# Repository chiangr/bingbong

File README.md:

# bingbong

The current interactive product site, engineering references, and hardware working files in one checkout. Start with [SESSION_HANDOFF.md](SESSION_HANDOFF.md) for the accepted design direction, source authority, verification results, and remaining work.

This handoff branch is `codex/assembly-handoff-2026-09-22` in [chiangr/bingbong](https://github.com/chiangr/bingbong). It preserves the earlier `master` history and mirrors the local project layout: the former repository-root firmware now lives under `firmware/`.

## Run the site

Install Node.js 24 LTS (or 22.12+) and run:

```sh
git clone --single-branch --branch codex/assembly-handoff-2026-09-22 https://github.com/chiangr/bingbong.git
cd bingbong/site
npm ci
npm run dev
```

Open http://localhost:5173/#inside for the exploded assembly study, or http://localhost:5173/ for the full fifteen-chapter experience. [The standalone HTML](site/artifact/bingbong.html) also opens directly in a browser without installing dependencies.

For a production preview:

```sh
npm run build
npm run preview
```

Open http://localhost:4173/#inside. Servers must be started on each laptop; no remote service is required.

## Project map

| Path | Contents |
| --- | --- |
| [site/](site/) | Current Three.js/Vite experience, all assets, source, scripts and documentation |
| [site/qa/](site/qa/) | Saved tests, 240 layout captures, independent reviews, Lighthouse report and videos |
| [DESIGN_MANUFACTURING_REPORT_2026-09-19.md](DESIGN_MANUFACTURING_REPORT_2026-09-19.md) | Latest engineering authority, including conflicts and open decisions |
| [REDESIGN_DECISION_2026-09-12.md](REDESIGN_DECISION_2026-09-12.md) | Earlier engineering decisions; superseded where the September 19 report conflicts |
| [firmware/](firmware/) | Existing ESP32-S2/BG95 bring-up code and current KiCad working files in `bingbong_pcb/` |
| [cad/](cad/), [cad-v2/](cad-v2/) | Existing mechanical and PCB design exports; these are not final production CAD for the illustrated reference build |
| [pcbway-fab/](pcbway-fab/), [datasheets/](datasheets/), [bom-scratch/](bom-scratch/) | Fabrication exports, component references and supporting analysis |

See [site/README.md](site/README.md) for interactions and verification commands. The website uses the engineering report's reference geometry; existing hardware files and firmware do not constitute a completed implementation of that design.

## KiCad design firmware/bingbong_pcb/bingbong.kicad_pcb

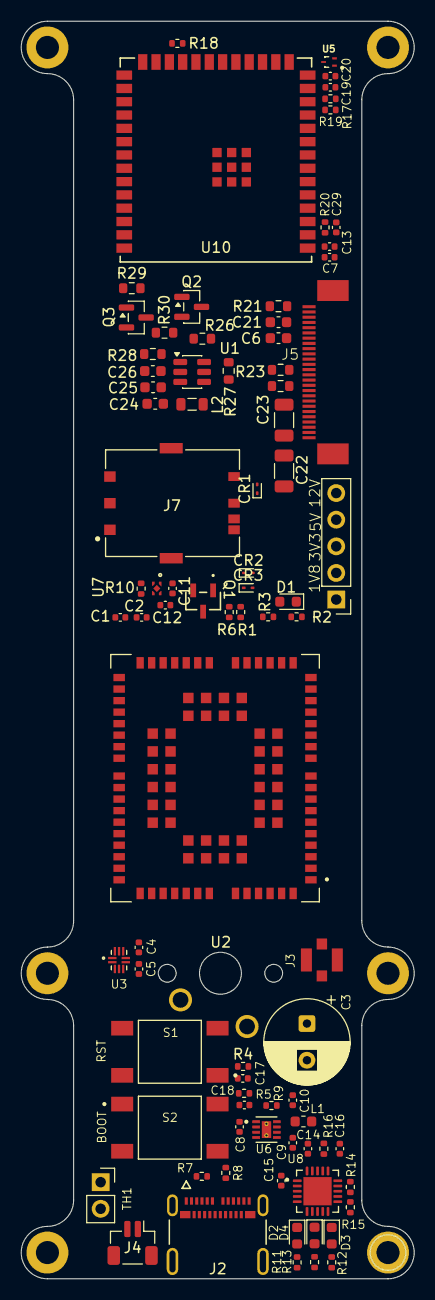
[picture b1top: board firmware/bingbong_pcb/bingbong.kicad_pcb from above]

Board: 2 copper layers, 37.5 x 120.0 mm, 85 parts (1 on the bottom side), 60 nets, no tracks yet.

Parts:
C1, C4, C5, C7, C17, C18, C19: 0.1uF; C_0402_1005Metric
C2, C11, C12, C29: 1uF; C_0402_1005Metric
C3: 470 uF; CP_Radial_D8.0mm_P3.50mm
C6, C21: 0.1uF; C_0603_1608Metric
C8, C9, C15: 10uF; C_0402_1005Metric
C10, C13, C20: 22uF; C_0402_1005Metric
C14, C16: 4.7uF; C_0402_1005Metric
C22, C23: 4.7uF; C_1206_3216Metric
C24, C25: 1uF; C_0603_1608Metric
C26: 220pF; C_0603_1608Metric
CR1, CR2, CR3: PESD5V0F1BLD_315; D_SOD-923
D1: RED LED; LED_0603_1608Metric
D2, D3, D4: LED; LED_0603_1608Metric
J2: 1054500101; MOLEX_1054500101
J3: CONMHF1-SMD-T; TE_CONMHF1-SMD-T
J4: Conn_01x02_Pin; JST_SH_BM02B-SRSS-TB_1x02-1MP_P1.00mm_Vertical
J5: Conn_01x28_Socket; Conn_Zif_26Pin
J6: Conn_01x05_Pin; PinHeader_1x05_P2.54mm_Vertical
J7: 2452808-1; TE_2452808-1
L1: 2.2uH; L_0603_1608Metric
L2: 22uH; L_0805_2012Metric
Q1: SOT-23; SOT-23-3_1P4X3P040_ONS
Q2: FDN340P; SOT-23
Q3: SS8050; SOT-23
R1, R14, R15, R18, R20: 10k; R_0402_1005Metric
R2, R6, R9, R10, R16: 100k; R_0402_1005Metric
R3, R11, R12, R13: 1k; R_0402_1005Metric
R4, R5, R17, R19: 0; R_0402_1005Metric
R7, R8: 5.1k; R_0402_1005Metric
R21: 680k; R_0603_1608Metric
R22, R23, R26, R30: 10k; R_0603_1608Metric
R27: 110k; R_0603_1608Metric
R28: 2k; R_0603_1608Metric
R29: 1k; R_0603_1608Metric
S1, S2: TS04-66-70-BK-100-SMT; SW_TS04-66-70-BK-100-SMT
SW1: SW_Push; SW_Cherry_MX_1.00u_PCB
TH1: 10k; PinSocket_1x02_P2.54mm_Vertical
U1: SOT-23-6
U2: BG95M3LA-64-SGNS; XCVR_BG95M3LA-64-SGNS
U3: SN74AVC2T245RSWR; QFN40P180X140X55-10N
U5: TPD2EUSB30ADRTR; SOTFL35P100X50-3N
U6: TPS62172DSGR; SON50P200X200X80-9N
U7: MIC5504-1.8YMT-TR; TDFN1010-4LD-PL-2_MCH
U8: MCP73871-2CCI_ML; QFN50P400X400X100-21N
U10: ESP32-S2-SOLO-2U-N4; ESP32-S2-SOLO-2U_EXP

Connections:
+1.8V: C4.1, C11.1, J6.2, R2.1, U3.7 (VCCA), U7.1 (VOUT)
+3.3V: C5.1, C6.1, C7.1, C9.1, C10.1, C12.1, C13.1, C21.1, J5.19, J5.21, J5.22, J6.3, L1.1, Q2.2 (S), R3.2, R9.1, R11.1, R12.1, R13.1, R20.2, R22.2, R23.2, R30.1, SW1.1, U3.6 (VCCB), U3.10 (DIR1), U6.6 (VOS), U7.4 (VIN), U8.9 (~TE), U10.2 (3V3)
+5V: C15.1, J2.A4 (VBUS_A4), J2.A9 (VBUS_A9), J2.B4 (VBUS_B4), J2.B9 (VBUS_B9), J6.4, U8.2 (VPCC), U8.18 (IN), U8.19 (IN__1)
+12V: C22.1, C25.1, C26.1, J5.2, J5.25, J6.5, R27.2, U1.2 (VOUT)
/ANT_MAIN: J3.1, U2.60 (ANT_MAIN)
/BG95 RX: U2.34 (MAIN_RXD), U3.9 (A2)
/BG95 TOGGLE POWER: R1.1, R6.1, U10.20 (IO12)
/BG95 TX: U2.35 (MAIN_TXD), U3.8 (A1)
/BG95_CLK: CR2.1, J7.C3 (CLK), U2.46 (USIM_CLK)
/BG95_IO: CR1.1, J7.C7 (I/O), U2.45 (USIM_DATA)
/BG95_RST: CR3.1, J7.C2 (RST), U2.44 (USIM_RST)
/BG95_VCC: J7.C1 (VCC), U2.43 (USIM_VDD)
/BOOT: R5.2, U10.27 (IO0)
/BTN: R18.2, SW1.2, U10.23 (IO21)
/CHARGE EN: R16.2, U8.17 (CE), U10.22 (IO14)
/EN: C29.2, R4.2, R20.1, U10.3 (EN)
/ESP32 RX: U3.5 (B1), U10.38 (IO2)
/ESP32 TX: U3.4 (B2), U10.39 (IO1)
/IO19: R19.2, U10.13 (IO19)
/IO20: R17.2, U10.14 (IO20)
/MIC EN: R10.2, U7.3 (EN), U10.21 (IO13)
/OLED RST: J5.16, U10.17 (IO9)
/OLED SCL: J5.12, R23.1, U10.18 (IO10)
/OLED SDA: J5.10, J5.11, R22.1, U10.19 (IO11)
/R1200 CE: U1.1 (CE), U10.12 (IO8)
/R1200 PWR EN: R29.2, U10.11 (IO18)
/SIM SW: J7.SW, U10.24 (IO33)
/SYS LOAD: C8.1, C14.1, U6.2 (VLN), U6.3 (EN), U8.1 (OUT), U8.20 (OUT__1)
/USB D+: C19.1, C20.1, J2.A6 (D1+), J2.B6 (D2+), R17.1, U5.1 (D+)
/USB D-: J2.A7 (D1-), J2.B7 (D2-), R19.1, U5.2 (D-)
/VBAT: C1.1, C2.1, C3.1, J4.2, TH1.2, U2.32 (VBAT_BB), U2.33 (VBAT_BB__1), U2.52 (VBAT_RF), U2.53 (VBAT_RF__1), U8.5 (THERM)
GND: C1.2, C2.2, C3.2, C4.2, C5.2, C6.2, C7.2, C8.2, C9.2, C10.2, C11.2, C12.2, C13.2, C14.2, C15.2, C16.2, C17.2, C18.2, C19.2, C20.2, C21.2, C22.2, C23.2, C24.2, C25.2, C29.1, CR1.2, CR2.2, CR3.2, J2.A1 (GND_A1), J2.A12 (GND_A12), J2.B1 (GND_B1), J2.B12 (GND_B12), J2.SH1 (SHIELD3), J2.SH2 (SHIELD4), J2.SH3 (SHIELD1), J2.SH4 (SHIELD2), J3.2, J3.3, J3.4, J4.1, J5.4, J5.5, J5.6, J5.7, J5.8, J5.9, J5.13, J5.14, J5.15, J5.17, J5.18, J5.20, J5.23, J5.27, J5.28, J6.1, J7.C5 (GND), J7.GND8 (SH), J7.GND9 (SH__1), Q1.1 (E), Q3.2 (E), R6.2, R7.2, R8.1, R10.1, R14.1, R15.1, R16.1, R18.1, R21.2, R26.1, S1.2, S1.4, S2.2, S2.4, TH1.1, U1.5 (GND), U2.3 (GND), U2.31 (GND__1), U2.47 (USIM_GND), U2.48 (GND__2), U2.50 (GND__3), U2.54 (GND__4), U2.55 (GND__5), U2.58 (GND__6), U2.59 (GND__7), U2.61 (GND__8), U2.62 (GND__9), U2.67 (GND__10), U2.68 (GND__11), U2.69 (GND__12), U2.70 (GND__13), U2.71 (GND__14), U2.72 (GND__15), U2.73 (GND__16), U2.74 (GND__17), U2.79 (GND__18), U2.80 (GND__19), U2.81 (GND__20), U2.82 (GND__21), U2.89 (GND__22), U2.90 (GND__23), U2.91 (GND__24), U2.100 (GND__25), U2.101 (GND__26), U2.102 (GND__27), U3.1 (DIR2), U3.2 (~OE), U3.3 (GND), U5.3 (GND), U6.1 (PGND), U6.4 (AGND), U6.5 (FB), U6.9 (EPAD), U7.2 (GND), U7.5 (GND), U8.3 (SEL), U8.4 (PROG2), U8.10 (VSS__1), U8.11 (VSS), U8.21 (EP), U10.1 (GND), U10.40 (GND), U10.41 (GND), U10.42 (GND), U10.43 (GND), U10.44 (GND), U10.45 (GND), U10.46 (GND), U10.47 (GND), U10.48 (GND), U10.49 (GND)
unnamed: C17.1, R4.1, S1.1, S1.3
unnamed: C18.1, R5.1, S2.1, S2.3
unnamed: C26.2, R28.2
unnamed: D1.2 (A), R3.1
unnamed: D1.1 (K), U2.21 (NET_STATUS)
unnamed: D2.2 (A), R11.2
unnamed: D2.1 (K), U8.6 (~PG)
unnamed: D3.2 (A), R12.2
unnamed: D3.1 (K), U8.8 (STAT1/*LBO)
unnamed: D4.2 (A), R13.2
unnamed: D4.1 (K), U8.7 (STAT2)
unnamed: J2.A5 (CC1), R7.1
unnamed: J2.B5 (CC2), R8.2
unnamed: C23.1, J5.3
unnamed: J5.24, R21.1
unnamed: Q1.2 (B), R1.2
unnamed: Q1.3 (C), U2.15 (PWRKEY)
unnamed: C24.1, L2.1, Q2.3 (D), U1.3 (VDD)
unnamed: Q2.1 (G), Q3.3 (C), R30.2
unnamed: Q3.1 (B), R29.1
unnamed: L2.2, U1.4 (Lx)
unnamed: R26.2, R27.1, R28.1, U1.6 (VFB)
unnamed: R2.2, U2.17 (~RESET)
unnamed: R9.2, U6.8 (PG)
unnamed: L1.2, U6.7 (SW)
unnamed: R14.2, U8.13 (PROG1)
unnamed: R15.2, U8.12 (PROG3)
unnamed: C16.1, U8.14 (VBAT__1), U8.15 (VBAT), U8.16 (VBAT_SENSE)

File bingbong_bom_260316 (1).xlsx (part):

Ryan Chiang |  | rychi@berkeley.edu |  |  |  |  |  |  |  |  |  |  |  |  |  | Total Price for Project
 |  |  |  |  |  |  |  |  |  |  |  |  |  |  |  | 68.7
Quantity | Purchase Status | Description (include component value if applicable) | Purchase URL | Reference Designator | Package/Case | Type | Assembly (YES/NO) | Side | Manufacturer Part # | Digi-key Part#/SKU | Price/unit ($) | Datasheet Link |  | Multiple | Total Qty | Total Price/part ($)
1.0 | Ordered | 470 µF 16 V Aluminum Electrolytic Capacitors Radial, Can 8000 Hrs @ 105°C | https://www.digikey.com/en/products/detail/rubycon/16ZLH470M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 | C3 | Radial, Can | Through Hole | YES | TOP | 16ZLH470MEFCT78X11.5 | 1189-3712-1-ND | 0.42 | https://www.rubycon.co.jp/wp-content/uploads/catalog-aluminu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 |  | 1.0 | 1 | 0.42
4.0 | Ordered | 1 µF ±10% 6.3V Ceramic Capacitor X5R 0402 (1005 Metric) | https://www.digikey.com/en/products/detail/taiyo-yuden/JMK10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 | C2, C11, C12, C29 | 402.0 | SMD | YES | TOP | JMK105BJ105KV-F | 587-1231-2-ND | 0.08 | https://ds.yuden.co.jp/TYCOMPAS/ut/detail?pn=JMK105BJ105KV-F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 |  | 1.0 | 4 | 0.32
7.0 | Ordered | 0.1 µF ±10% 25V Ceramic Capacitor X5R 0402 (1005 Metric) | https://www.digikey.com/en/products/detail/samsung-electro-m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 | C1, C4, C5, C7, C17, C18, C19 | 402.0 | SMD | YES | TOP | CL05A104KA5NNNC | 1276-1043-2-ND | 0.08 | https://mm.digikey.com/Volume0/opasdata/d220001/medias/docus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 |  | 1.0 | 7 | 0.56
2.0 | Ordered | 100 pF ±10% 50V Ceramic Capacitor X7R 0603 (1608 Metric) | https://www.digikey.com/en/products/detail/kemet/C0603C101K5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 | C6, C21 | 603.0 | SMD | YES | TOP | C0603C101K5RACAUTO7411 | 399-C0603C101K5RACAUTO7411CT-ND | 0.12 | https://yageogroup.com/content/datasheet/asset/file/KEM_C102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 |  | 1.0 | 2 | 0.24
2.0 | Ordered | 4.7 µF Molded Tantalum Capacitors 25 V 1206 (3216 Metric) 6Ohm | https://www.digikey.com/en/products/detail/kemet/T491A475K02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 | C22, C23 | 1206.0 | SMD | YES | TOP | T491A475K025AT | 399-10128-1-ND | 0.44 | https://yageogroup.com/content/datasheet/asset/file/KEM_T2005_T491 |  | 1.0 | 2 | 0.88
1.0 | Ordered | 220 pF ±10% 25V Ceramic Capacitor X7R 0603 (1608 Metric) | https://www.digikey.com/en/products/detail/w%C3%BCrth-elektr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 | C26 | 603.0 | SMD | YES | TOP | 8.85012206055E11 | 732-7974-1-ND | 0.1 | https://www.we-online.com/components/products/datasheet/8850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 |  | 1.0 | 1 | 0.1
3.0 | Ordered | 22 µF ±20% 6.3V Ceramic Capacitor X5R 0402 (1005 Metric) | https://www.digikey.com/en/products/detail/murata-electronic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 | C10, C13, C20 | 402.0 | SMD | YES | TOP | GRM158R60J226ME01D | 490-GRM158R60J226ME01DCT-ND | 0.37 | https://search.murata.co.jp/Ceramy/image/img/A01X/G101/ENG/G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 |  | 1.0 | 3 | 1.11
3.0 | Ordered | 10 µF ±20% 10V Ceramic Capacitor X5R 0402 (1005 Metric) | https://www.digikey.com/en/products/detail/murata-electronic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 | C8, C9, C15 | 402.0 | SMD | YES | TOP | GRM155R61A106ME11D | 490-GRM155R61A106ME11DCT-ND | 0.08 | https://search.murata.co.jp/Ceramy/image/img/A01X/G101/ENG/G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 |  | 1.0 | 3 | 0.24
2.0 | Ordered | 4.7 µF ±20% 10V Ceramic Capacitor X5R 0402 (1005 Metric) | https://www.digikey.com/en/products/detail/samsung-electro-m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 | C14, C16 | 402.0 | SMD | YES | TOP | CL05A475MP5NRNC | 1276-1482-1-ND | 0.1 | https://mm.digikey.com/Volume0/opasdata/d220001/medias/docus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 |  | 1.0 | 2 | 0.2
2.0 | Ordered | 1 µF ±10% 16V Ceramic Capacitor X7R 0603 (1608 Metric) | https://www.digikey.com/en/products/detail/kemet/C0603C105K4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 | C24, C25 | 603.0 | SMD | YES | TOP | C0603C105K4RACTU | 399-C0603C105K4RACTUCT-ND | 0.08 | https://yageogroup.com/content/datasheet/asset/file/KEM_C100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 |  | 1.0 | 2 | 0.16
3.0 | Ordered | Clamp Ipp Tvs Diode Surface Mount SOD-923 | https://www.digikey.com/en/products/detail/onsemi/ESD9B5.0ST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 | CR1, CR2, CR3 | SOD-923 | SMD | YES | TOP | ESD9B5.0ST5G | ESD9B5.0ST5GOSCT-ND | 0.1 | https://www.digikey.com/en/products/detail/onsemi/ESD9B5.0ST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 |  | 1.0 | 3 | 0.3
2.0 | Ordered | Red 630nm LED Indication - Discrete 1.9V 0603 (1608 Metric) | https://www.digikey.com/en/products/detail/w-rth-elektronik/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 | D1, D3 | 603.0 | SMD | YES | TOP | 150060SS75000 | 732-4979-1-ND | 0.15 | https://www.digikey.com/en/products/detail/w-rth-elektronik/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 |  | 1.0 | 2 | 0.3
2.0 | Ordered | Green 573nm LED Indication - Discrete 2V 0603 (1608 Metric) | https://www.digikey.com/en/products/detail/w%C3%BCrth-elektr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 | D2, D4 | 603.0 | SMD | YES | TOP | 150060VS55040 | 732-12017-1-ND | 0.19 | https://www.we-online.com/components/products/datasheet/1500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 |  | 1.0 | 2 | 0.38
1.0 | Ordered | USB-C (USB TYPE-C) USB 3.2 Gen 2 (USB 3.1 Gen 2, Superspeed + (USB 3.1)) Recept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 | https://www.digikey.com/en/products/detail/molex/1054500101/5843891 | J2 | -- | SMD, Through Hole | YES | TOP | 1.054500101E9 | WM12856CT-ND | 2.4 | https://www.molex.com/pdm_docs/ps/PS-105448-001.pdf |  | 1.0 | 1 | 2.4
1.0 | Ordered | U.FL (UMCC) Connector Jack, Male Pin 50 Ohms Surface Mount Solder | https://www.digikey.com/en/products/detail/te-connectivity-l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 | J3 | -- | SMD | YES | TOP | CONMHF1-SMD-T | 343-CONMHF1-SMD-TCT-ND | 0.21 | https://www.te.com/commerce/DocumentDelivery/DDEController?A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 |  | 1.0 | 1.0 | 0.21
1.0 | Ordered | Connector Header Surface Mount 2 position 0.039" (1.00mm) | https://www.digikey.com/en/products/detail/jst-sales-america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 | J4 | -- | SMD | YES | TOP | BM02B-SRSS-TBT | 455-BM02B-SRSS-TBTCT-ND | 0.56 | https://www.jst-connector.com/datasheet/jst-connector/BM02B-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 |  | 1.0 | 1.0 | 0.56
1.0 | Ordered | 26 Pins 0.5mm Pitch ZIF Connector (FPC Connector) | https://www.buydisplay.com/white-1-8-inch-256x32-oled-displa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 | J5 | -- | SMD | YES | TOP | -- | -- | 0.16 | https://www.buydisplay.com/download/connector/ER-CON26HT-1.pdf |  | 1.0 | 1 | 0.16
1.0 | Ordered | 8 (6 + 2) Position Card Connector NANO SIM Surface Mount, Right Angle Gold | https://www.digikey.com/en/products/detail/te-connectivity-l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 | J7 | -- | SMD | YES | TOP | 2452808-1 | 343-2452808-1CT-ND | 1.36 | https://www.te.com/usa-en/product-2452808-1.datasheet.pdf |  | 1.0 | 1 | 1.36
1.0 | Ordered | 2.2 µH Shielded Multilayer Inductor 500 mA 250mOhm 0603 (1608 Metric) | https://www.digikey.com/en/products/detail/tdk/MLZ1608A2R2WT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 | L1 | 603.0 | SMD | YES | TOP | MLZ1608A2R2WTD25 | 445-MLZ1608A2R2WTD25CT-ND | 0.13 | https://product.tdk.com/en/system/files?file=dam/doc/product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 |  | 1.0 | 1 | 0.13
1.0 | Ordered | 22 µH Shielded Multilayer Inductor 220 mA 1.25Ohm 0805 (2012 Metric) | https://www.digikey.com/en/products/detail/tdk-corporation/M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 | L2 | 805.0 | SMD | YES | TOP | MLZ2012P220WT000 | 445-15751-1-ND | 0.1 | https://product.tdk.com/en/system/files?file=dam/doc/product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 |  | 1.0 | 1 | 0.1
1.0 | Ordered | Bipolar (BJT) Transistor NPN 40 V 600 mA 300MHz 300 mW Surface Mount SOT-23-3 (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 | https://www.digikey.com/en/products/detail/onsemi/SMMBT2222A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 | Q1 | SOT-23-3 | SMD | YES | TOP | SMMBT2222ALT3G | SMMBT2222ALT3GOSCT-ND | 0.18 | https://www.onsemi.com/pdf/datasheet/mmbt2222lt1-d.pdf |  | 1.0 | 1 | 0.18
1.0 | Ordered | P-Channel 20 V 1.6A (Ta) 500mW (Ta) Surface Mount SOT-23-3 | https://www.digikey.com/en/products/detail/onsemi/FDN338P/45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 | Q2 | SOT-23-3 | SMD | YES | TOP | FDN338P | FDN338PCT-ND | 0.68 | https://www.onsemi.com/pdf/datasheet/fdn338p-d.pdf |  | 1.0 | 1 | 0.68
1.0 | Ordered | Bipolar (BJT) Transistor NPN 25 V 1.5 A 100MHz 300 mW Surface Mount SOT-23 | https://www.digikey.com/en/products/detail/shenzhen-slkormic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 | Q3 | TO-236-3, SC-59, SOT-23-3 | SMD | YES | TOP | SS8050 | 5399-SS8050CT-ND | 0.1 | -- |  | 1.0 | 1 | 0.1
2.0 | Ordered | Tactile Switch SPST-NO Top Actuated Surface Mount | https://www.digikey.com/en/products/detail/same-sky-formerly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 | S1, S2 | -- | SMD | YES | TOP | TS04-66-70-BK-100-SMT | 2223-TS04-66-70-BK-100-SMT-ND | 0.19 | https://www.cuidevices.com/product/resource/ts04.pdf |  | 1.0 | 2 | 0.38
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
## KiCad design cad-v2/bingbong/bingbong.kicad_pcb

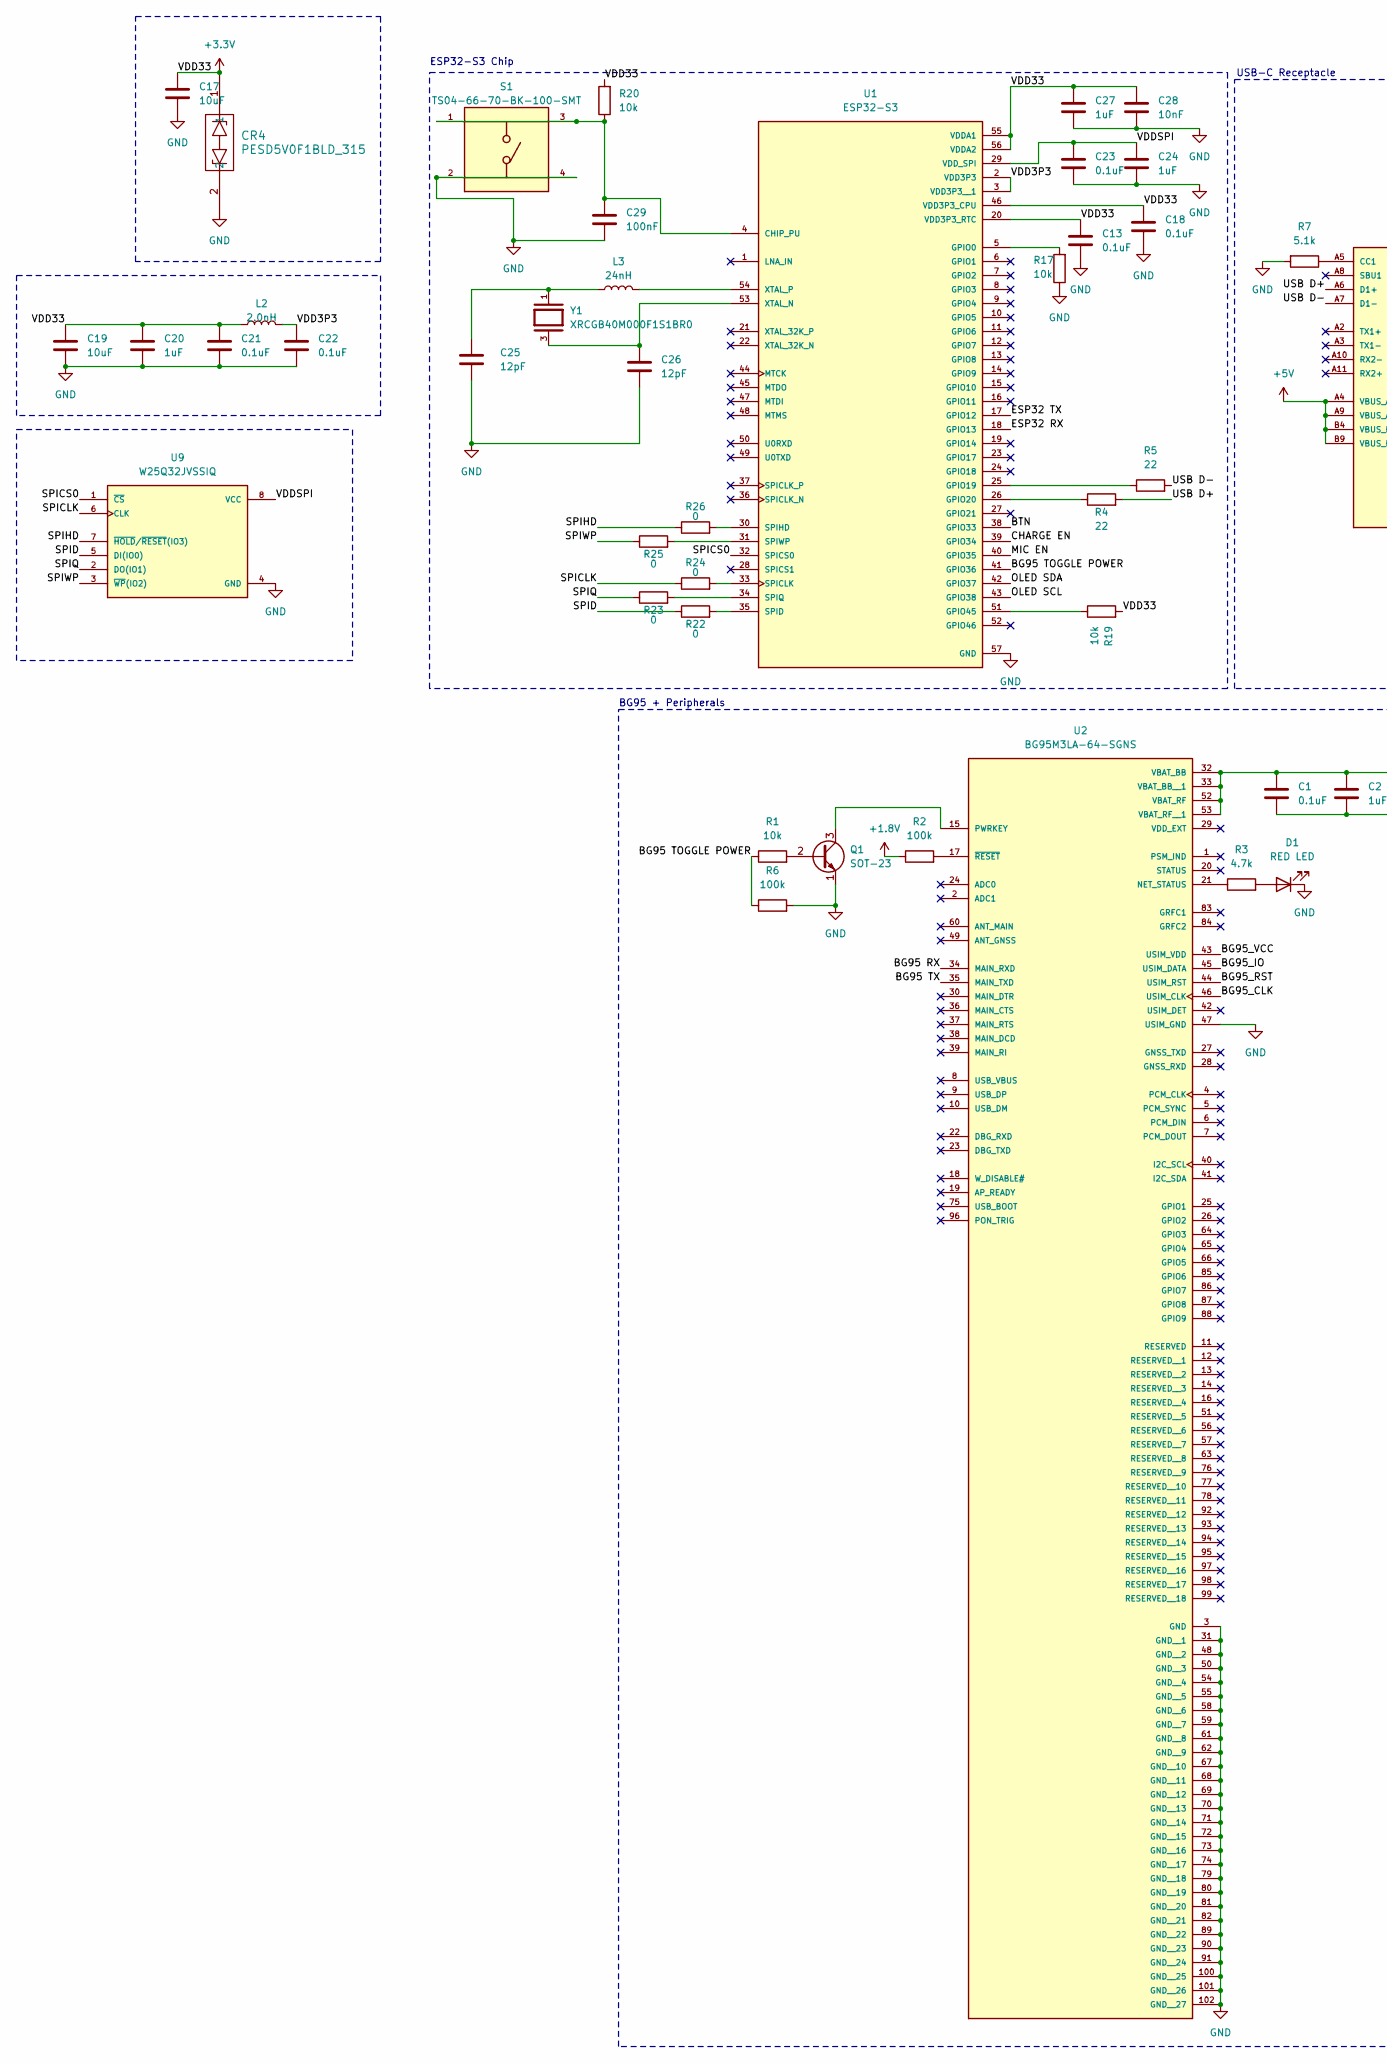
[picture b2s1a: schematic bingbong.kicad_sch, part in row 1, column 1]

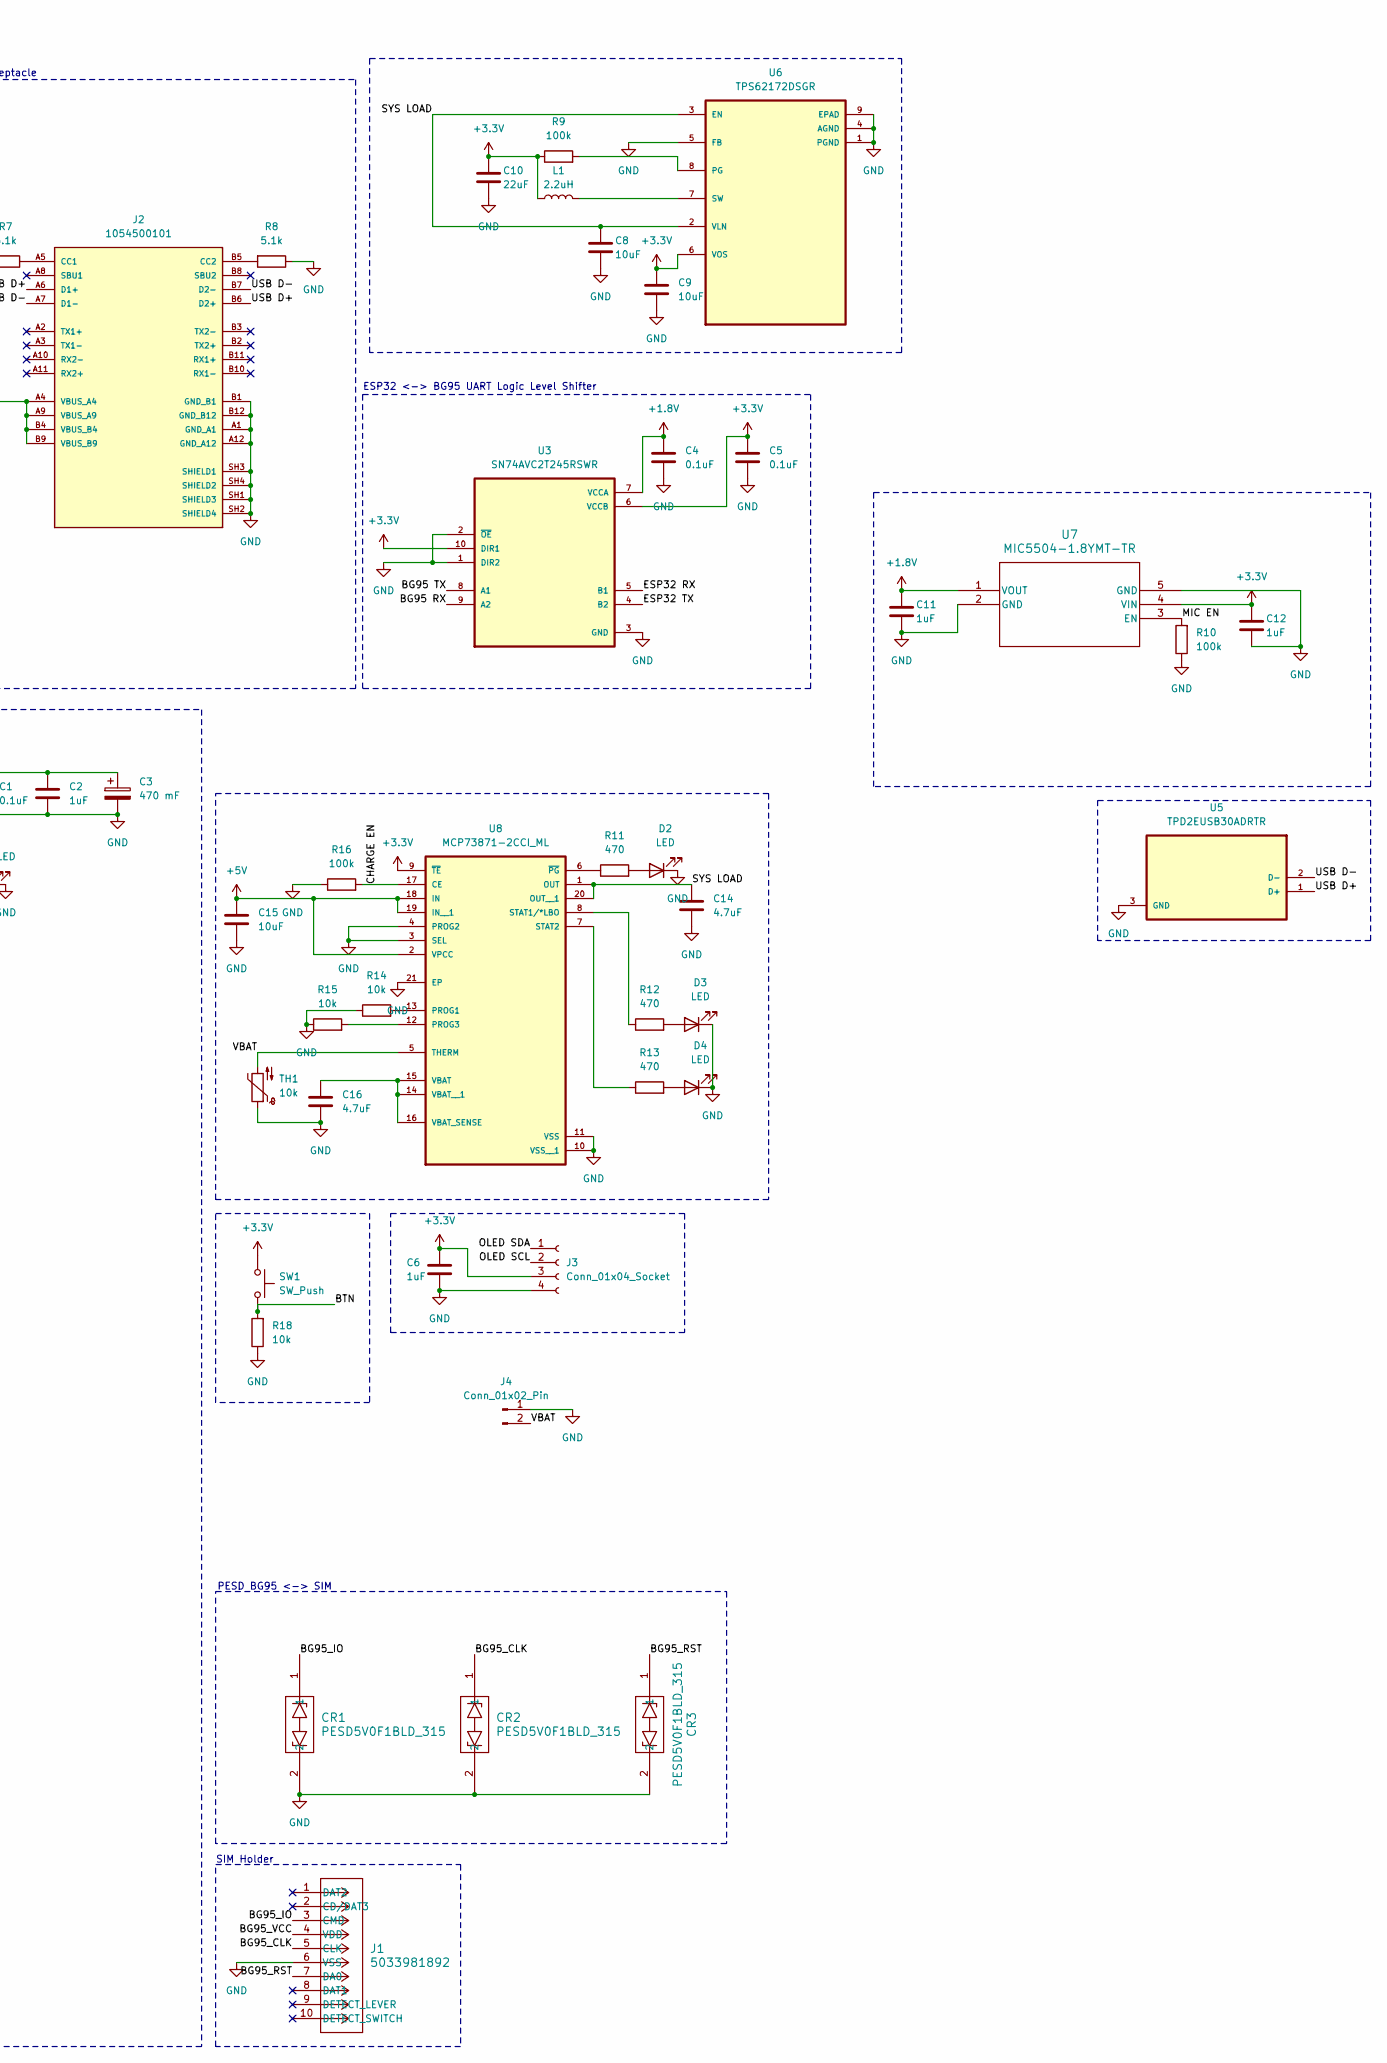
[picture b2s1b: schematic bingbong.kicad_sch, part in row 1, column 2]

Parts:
C1, C4, C5, C13, C18, C21, C22, C23: 0.1uF; C_0402_1005Metric
C2, C6, C11, C12, C20, C24, C27: 1uF; C_0402_1005Metric
C3: 470 mF; CP_Radial_D8.0mm_P3.50mm
C8, C9, C15, C17, C19: 10uF; C_0402_1005Metric
C10: 22uF; C_0402_1005Metric
C14, C16: 4.7uF; C_0402_1005Metric
C25, C26: 12pF; C_0402_1005Metric
C28: 10nF; C_0402_1005Metric
C29: 100nF; C_0402_1005Metric
CR1, CR2, CR3, CR4: PESD5V0F1BLD_315; DFN1006D-2_SOD882D_NEX
D1: RED LED; LED_0603_1608Metric
D2, D3, D4: LED; LED_0603_1608Metric
J1: 5033981892; CONN_503398-1892_MOL
J2: 1054500101; MOLEX_1054500101; PARTREV A7
J3: Conn_01x04_Socket; PinSocket_1x04_P2.54mm_Vertical
J4: Conn_01x02_Pin; PinHeader_1x02_P1.00mm_Vertical
L1: 2.2uH; L_0603_1608Metric
L2: 2.0nH; L_0603_1608Metric
L3: 24nH; L_0603_1608Metric
Q1: SOT-23; SOT-23-3_1P4X3P040_ONS
R1, R14, R15, R17, R18, R19, R20: 10k; R_0402_1005Metric
R2, R6, R9, R10, R16: 100k; R_0402_1005Metric
R3: 4.7k; R_0402_1005Metric
R4, R5: 22; R_0402_1005Metric
R7, R8: 5.1k; R_0402_1005Metric
R11, R12, R13: 470; R_0402_1005Metric
R22, R23, R24, R25, R26: 0; R_0402_1005Metric
S1: TS04-66-70-BK-100-SMT; SW_TS04-66-70-BK-100-SMT; PARTREV 1.0
SW1: SW_Push; SW_Cherry_MX_1.00u_PCB
TH1: 10k; PinSocket_1x02_P2.54mm_Vertical
U1: ESP32-S3; IC_ESP32-S3; PARTREV v1.2
U2: BG95M3LA-64-SGNS; XCVR_BG95M3LA-64-SGNS
U3: SN74AVC2T245RSWR; QFN40P180X140X55-10N
U5: TPD2EUSB30ADRTR; SOTFL35P100X50-3N
U6: TPS62172DSGR; SON50P200X200X80-9N
U7: MIC5504-1.8YMT-TR; TDFN1010-4LD-PL-2_MCH
U8: MCP73871-2CCI_ML; QFN50P400X400X100-21N
U9: W25Q32JVSSIQ; SOIC127P790X216-8N
Y1: XRCGB40M000F1S1BR0; OSC_XRCGB40M000F1S1BR0; PARTREV N/A

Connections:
+1.8V: C4.1, C11.1, R2.1, U3.7 (VCCA), U7.1 (VOUT)
+3.3V: C5.1, C6.1, C9.1, C10.1, C12.1, C13.1, C17.1, C18.1, C19.1, C20.1, C21.1, C27.1, C28.1, CR4.1, J3.3, L1.1, L2.1, R9.1, R19.2, R20.2, SW1.1, U1.20 (VDD3P3_RTC), U1.46 (VDD3P3_CPU), U1.55 (VDDA1), U1.56 (VDDA2), U3.6 (VCCB), U3.10 (DIR1), U6.6 (VOS), U7.4 (VIN), U8.9 (~TE)
+5V: C15.1, J2.A4 (VBUS_A4), J2.A9 (VBUS_A9), J2.B4 (VBUS_B4), J2.B9 (VBUS_B9), U8.2 (VPCC), U8.18 (IN), U8.19 (IN__1)
/BG95 RX: U2.34 (MAIN_RXD), U3.9 (A2)
/BG95 TOGGLE POWER: R1.1, R6.1, U1.41 (GPIO36)
/BG95 TX: U2.35 (MAIN_TXD), U3.8 (A1)
/BG95_CLK: CR2.1, J1.5 (CLK), U2.46 (USIM_CLK)
/BG95_IO: CR1.1, J1.3 (CMD), U2.45 (USIM_DATA)
/BG95_RST: CR3.1, J1.7 (DA0), U2.44 (USIM_RST)
/BG95_VCC: J1.4 (VDD), U2.43 (USIM_VDD)
/BTN: R18.2, SW1.2, U1.38 (GPIO33)
/CHARGE EN: R16.2, U1.39 (GPIO34), U8.17 (CE)
/ESP32 RX: U1.18 (GPIO13), U3.5 (B1)
/ESP32 TX: U1.17 (GPIO12), U3.4 (B2)
/MIC EN: R10.2, U1.40 (GPIO35), U7.3 (EN)
/OLED SCL: J3.2, U1.43 (GPIO38)
/OLED SDA: J3.1, U1.42 (GPIO37)
/SPICLK: R24.1, U9.6 (CLK)
/SPICS0: U1.32 (SPICS0), U9.1 (~CS)
/SPID: R22.1, U9.5 (DI(IO0))
/SPIHD: R26.1, U9.7 (~HOLD/~RESET(IO3))
/SPIQ: R23.1, U9.2 (DO(IO1))
/SPIWP: R25.1, U9.3 (~WP(IO2))
/SYS LOAD: C8.1, C14.1, U6.2 (VLN), U6.3 (EN), U8.1 (OUT), U8.20 (OUT__1)
/USB D+: J2.A6 (D1+), J2.B6 (D2+), R4.2, U5.1 (D+)
/USB D-: J2.A7 (D1-), J2.B7 (D2-), R5.2, U5.2 (D-)
/VBAT: J4.2, TH1.2, U8.5 (THERM)
/VDD3P3: C22.1, L2.2, U1.2 (VDD3P3), U1.3 (VDD3P3__1)
/VDDSPI: C23.1, C24.1, U1.29 (VDD_SPI), U9.8 (VCC)
GND: C1.2, C2.2, C3.2, C4.2, C5.2, C6.2, C8.2, C9.2, C10.2, C11.2, C12.2, C13.2, C14.2, C15.2, C16.2, C17.2, C18.2, C19.2, C20.2, C21.2, C22.2, C23.2, C24.2, C25.1, C26.1, C27.2, C28.2, C29.1, CR1.2, CR2.2, CR3.2, CR4.2, D1.1 (K), D2.1 (K), D3.1 (K), D4.1 (K), J1.6 (VSS), J2.A1 (GND_A1), J2.A12 (GND_A12), J2.B1 (GND_B1), J2.B12 (GND_B12), J2.SH1 (SHIELD3), J2.SH2 (SHIELD4), J2.SH3 (SHIELD1), J2.SH4 (SHIELD2), J3.4, J4.1, Q1.1 (E), R6.2, R7.2, R8.1, R10.1, R14.1, R15.1, R16.1, R17.1, R18.1, S1.2, S1.4, TH1.1, U1.57 (GND), U2.3 (GND), U2.31 (GND__1), U2.47 (USIM_GND), U2.48 (GND__2), U2.50 (GND__3), U2.54 (GND__4), U2.55 (GND__5), U2.58 (GND__6), U2.59 (GND__7), U2.61 (GND__8), U2.62 (GND__9), U2.67 (GND__10), U2.68 (GND__11), U2.69 (GND__12), U2.70 (GND__13), U2.71 (GND__14), U2.72 (GND__15), U2.73 (GND__16), U2.74 (GND__17), U2.79 (GND__18), U2.80 (GND__19), U2.81 (GND__20), U2.82 (GND__21), U2.89 (GND__22), U2.90 (GND__23), U2.91 (GND__24), U2.100 (GND__25), U2.101 (GND__26), U2.102 (GND__27), U3.1 (DIR2), U3.2 (~OE), U3.3 (GND), U5.3 (GND), U6.1 (PGND), U6.4 (AGND), U6.5 (FB), U6.9 (EPAD), U7.2 (GND), U7.5 (GND), U8.3 (SEL), U8.4 (PROG2), U8.10 (VSS__1), U8.11 (VSS), U8.21 (EP), U9.4 (GND)
unnamed: C25.2, L3.1, Y1.1
unnamed: D1.2 (A), R3.2
unnamed: D2.2 (A), R11.2
unnamed: D3.2 (A), R12.2
unnamed: D4.2 (A), R13.2
unnamed: J2.A5 (CC1), R7.1
unnamed: J2.B5 (CC2), R8.2
unnamed: Q1.2 (B), R1.2
unnamed: Q1.3 (C), U2.15 (PWRKEY)
unnamed: C29.2, R20.1, S1.1, S1.3, U1.4 (CHIP_PU)
unnamed: R17.2, U1.5 (GPIO0)
unnamed: R5.1, U1.25 (GPIO19)
unnamed: R4.1, U1.26 (GPIO20)
unnamed: R19.1, U1.51 (GPIO45)
unnamed: R24.2, U1.33 (SPICLK)
unnamed: R22.2, U1.35 (SPID)
unnamed: R26.2, U1.30 (SPIHD)
unnamed: R23.2, U1.34 (SPIQ)
unnamed: R25.2, U1.31 (SPIWP)
unnamed: C26.2, U1.53 (XTAL_N), Y1.3
unnamed: L3.2, U1.54 (XTAL_P)
unnamed: R3.1, U2.21 (NET_STATUS)
unnamed: C1.1, C2.1, C3.1, U2.32 (VBAT_BB), U2.33 (VBAT_BB__1), U2.52 (VBAT_RF), U2.53 (VBAT_RF__1)
unnamed: R2.2, U2.17 (~RESET)
unnamed: R9.2, U6.8 (PG)
unnamed: L1.2, U6.7 (SW)
unnamed: R14.2, U8.13 (PROG1)
unnamed: R15.2, U8.12 (PROG3)
unnamed: R12.1, U8.8 (STAT1/*LBO)
unnamed: R13.1, U8.7 (STAT2)
unnamed: C16.1, U8.14 (VBAT__1), U8.15 (VBAT), U8.16 (VBAT_SENSE)
unnamed: R11.1, U8.6 (~PG)

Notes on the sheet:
USB-C Receptacle
BG95 + Peripherals
SIM Holder
ESP32 <-> BG95 UART Logic Level Shifter
ESP32-S3 Chip
PESD BG95 <-> SIM

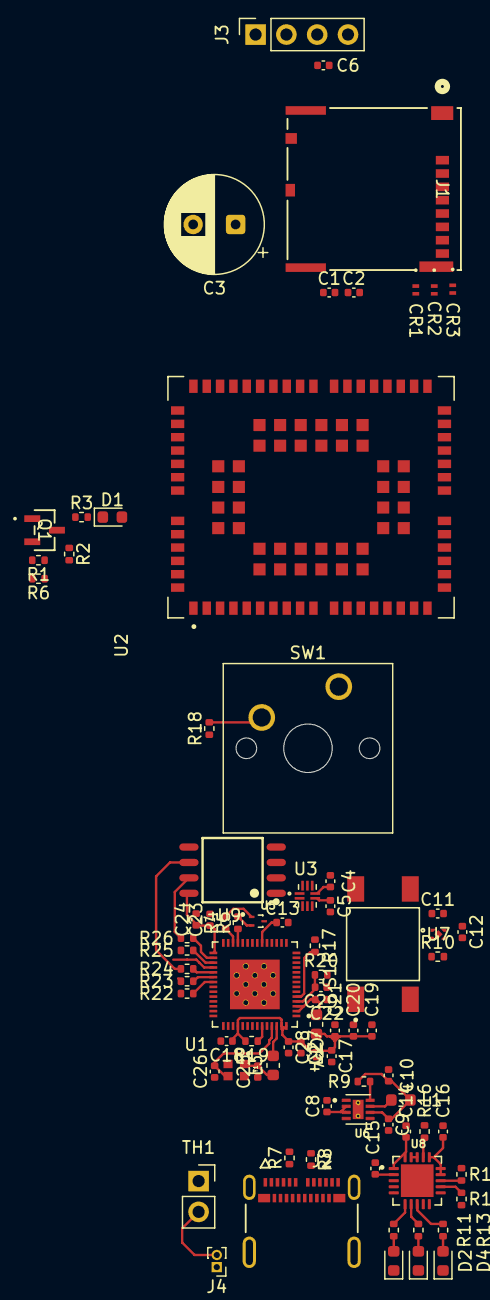
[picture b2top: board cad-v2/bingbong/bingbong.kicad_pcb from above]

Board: 2 copper layers, 81 parts (0 on the bottom side), 62 nets.

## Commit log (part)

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2026-06-06 bingbong
